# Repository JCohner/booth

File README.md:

# Booth Controller

Using ~1000 NeoPixels with FastLED library we are controlling a custom built DJ booths lighting.
The NeoPixels are organzied into rectangles on a DJ of which the light difuses around the rectnagle. 
This is using the SAMD21 broken out via the arduino nano 33 iot board. 

## Code Organization
* `booth_controller` contains the arduino sketch
  * `booth_controller.ino`
    * instantiates the DMX receiver very inspired by [this library](https://github.com/claudeheintz/LXSAMD21DMX/tree/master)
    * instantiates the custom LightingArrayController object
    * overrides the standard Serial1 handler SERCOM5 to specifically parse DMX inputs from the RS485 transciever 
    * sets up the dmx object and light controller
    * grabs dmx data and passes it to the light controller to map to rectangles
  * lighting_array_controller
    * **note** in both .h and .cpp file there is auto generated code parsed from the csv that keeps the rectangles aligned with reality. See rect_gen.py for more. 
    * **important** holds array of CRGB leds from FastLED 
    * handles business logic of holding array of rectangles and passing dmx channels to their relevant rectangle
    * critically calls FastLED.show()
  * rectangle
    * mechanisim to map global array of LEDs to given logical rectangle
    * has rectangle specific dmx_update mechanism which takes mapped dmx channels and translates to LED CRGB values
  * dmx
    * does dmx things, neat protocol. thanks to claudeheintz
* requirements.txt, rect_gen.py, rects.csv
  * all convinience things for autogenerating cpp code to map the rectangles
* Makefile
  * compile - compiles 'primary' and 'secondary' to cover both arduinos
  * deploy_[primary, secondary] - deploys relevant binary to MCU

## TODO attach pictures it looks sweet take my word for it for now.

### Notes:
Added: `void SERCOM5_Handler() __attribute__((weak));` to the relevant variants.cpp file such that I could overwrite the SERCOM5 handler being used for Serial1 to parse out the DMX messages

It seems my one nano was just not powerful enough to write to all 1000+ LEDs, I put another on the DMX bus and mapped it to the channels my first couldn't meet.

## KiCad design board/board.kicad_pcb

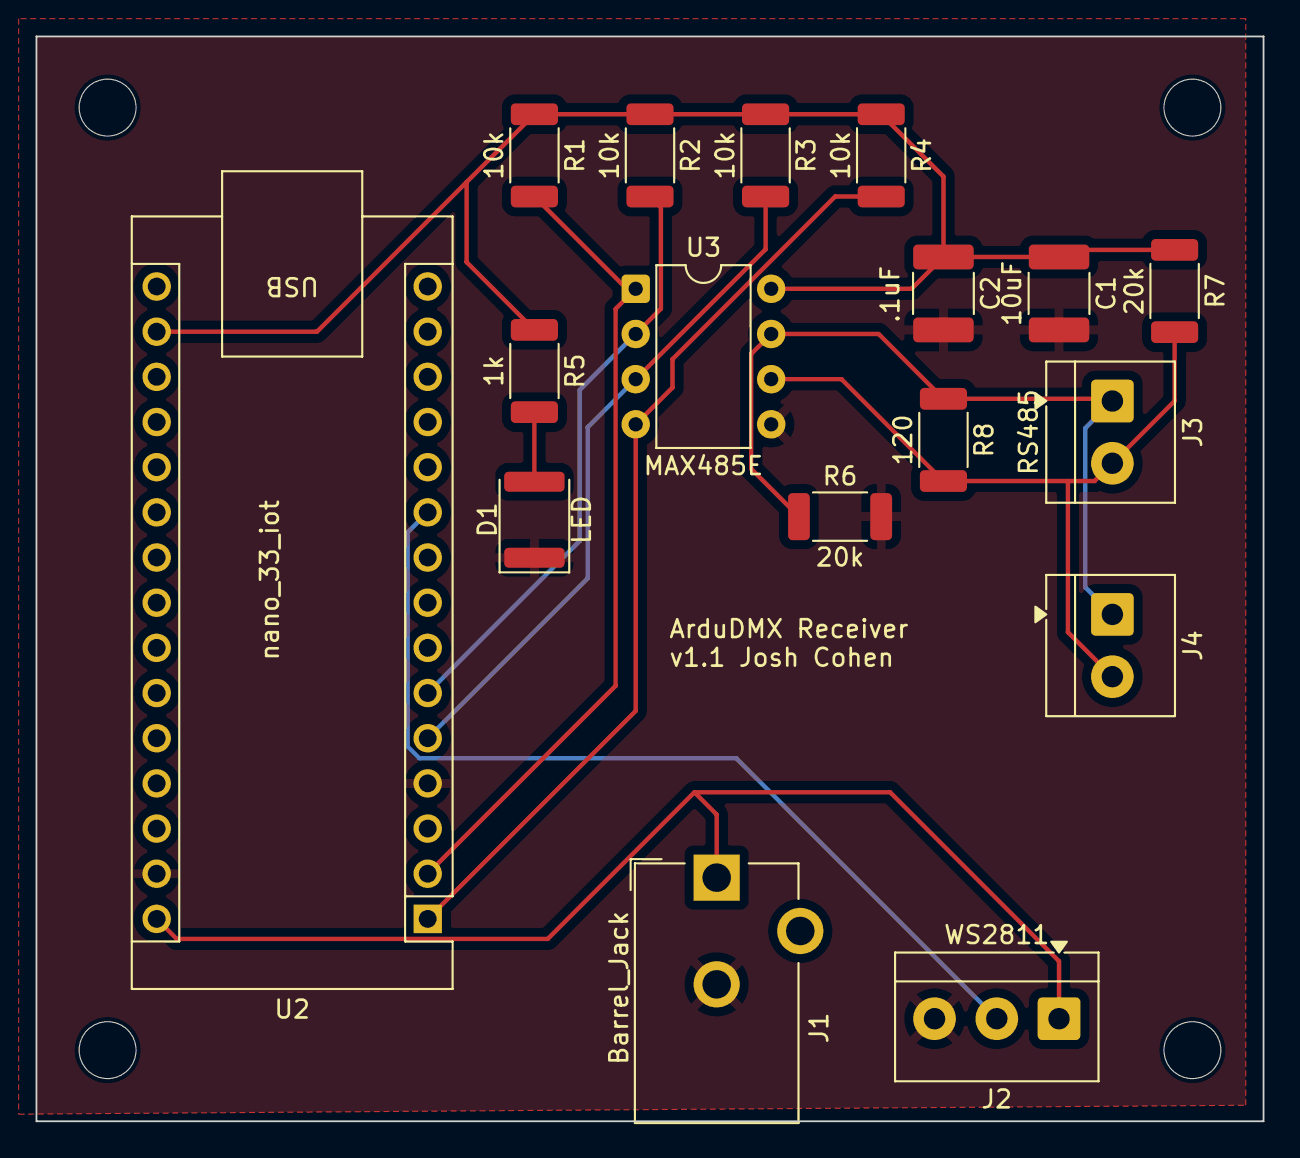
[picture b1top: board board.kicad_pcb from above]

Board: 2 copper layers, 69.0 x 61.0 mm, 21 parts (0 on the bottom side), 11 nets.

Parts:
C1: 10uF; C_1812_4532Metric
C2: .1uF; C_1812_4532Metric
D1: LED; LED_1812_4532Metric
H1, H2, H3, H4: MountingHole_Pad; MountingHole_3.2mm_M3
J1: Barrel_Jack; BarrelJack_CUI_PJ-102AH_Horizontal
J2: WS2811; TerminalBlock_4Ucon_1x03_P3.50mm_Horizontal
J3, J4: RS485; TerminalBlock_4Ucon_1x02_P3.50mm_Horizontal
R1, R2, R3, R4: 10k; R_2010_5025Metric
R5: 1k; R_2010_5025Metric
R6, R7: 20k; R_2010_5025Metric
R8: 120; R_2010_5025Metric
U2: nano_33_iot; Arduino_Nano
U3: MAX485E; DIP-8_W7.62mm

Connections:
+3.3V: C1.1, C2.1, R1.1, R2.1, R3.1, R4.1, R5.1, R7.1, U2.17 (3v3), U3.8 (VCC)
+5V: J1.1, J2.1, U2.30 (VIn)
/DE: R3.2, U2.5 (DE), U3.3 (DE)
/DI: R4.2, U2.1 (DI|tx), U3.4 (DI)
/RE: R2.2, U2.6 (RE), U3.2 (~RE)
/RO: R1.2, U2.2 (RO|rx), U3.1 (RO)
/cnt_sign: J2.2, U2.10 (cnt_sig)
GND: C1.2, C2.2, D1.1 (K), J1.2, J2.3, R6.2, U2.4 (GND), U2.29 (GND), U3.5 (GND)
unnamed: D1.2 (A), R5.2
unnamed: J3.1, J4.1, R6.1, R8.1, U3.7 (B)
unnamed: J3.2, J4.2, R7.2, R8.2, U3.6 (A)

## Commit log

2025-04-19 init
2025-04-19 gott reading value in
2025-04-19 cooking
2025-04-19 back
2025-04-19 having fun with nick
2025-04-19 fixed! got sine
2025-04-20 fastled
2025-04-21 switched to fastled
2025-04-21 stash
2025-04-21 regions?
2025-04-21 stashing
2025-04-21 got it!
2025-04-21 smart way
2025-04-21 changing fnames
2025-04-21 got twinkle!
2025-04-21 got offset
2025-04-21 rename
2025-04-21 made num rectangles a pound define
2025-04-21 feat: got static member variable id
2025-04-23 loop timing
2025-04-29 switch to nano 33 iot
2025-05-17 clean
2025-05-17 getting DMX in there
2025-05-17 cooking-with-gas
2025-05-23 making it real
2025-05-23 got 14
2025-05-23 got a rectangle to c code parser with brandongit add -u
2025-05-23 patched rect parser bug
2025-05-25 latest
2025-05-27 more rects
2025-05-28 big change
2025-05-28 got data rates happy
2025-05-28 baby steps
2025-05-29 closer
2025-05-29 best yet
2025-05-29 better py
2025-05-29 making gen rect better
2025-05-29 i'm not sure whats being so slow
2025-05-31 figured it out
2025-05-31 feat: bringing it back to one piece of source code thats compiled twice one for each dmx device with given paramters loaded in automatically
2025-05-31 feat: organzied so we can have it do the h file too
2025-06-01 feat: got master dimmer, finished automating generation of specific h file implementations
2025-06-01 clean up, minor document
2025-08-17 board v1.1
2025-08-17 needed to work with raw max485
